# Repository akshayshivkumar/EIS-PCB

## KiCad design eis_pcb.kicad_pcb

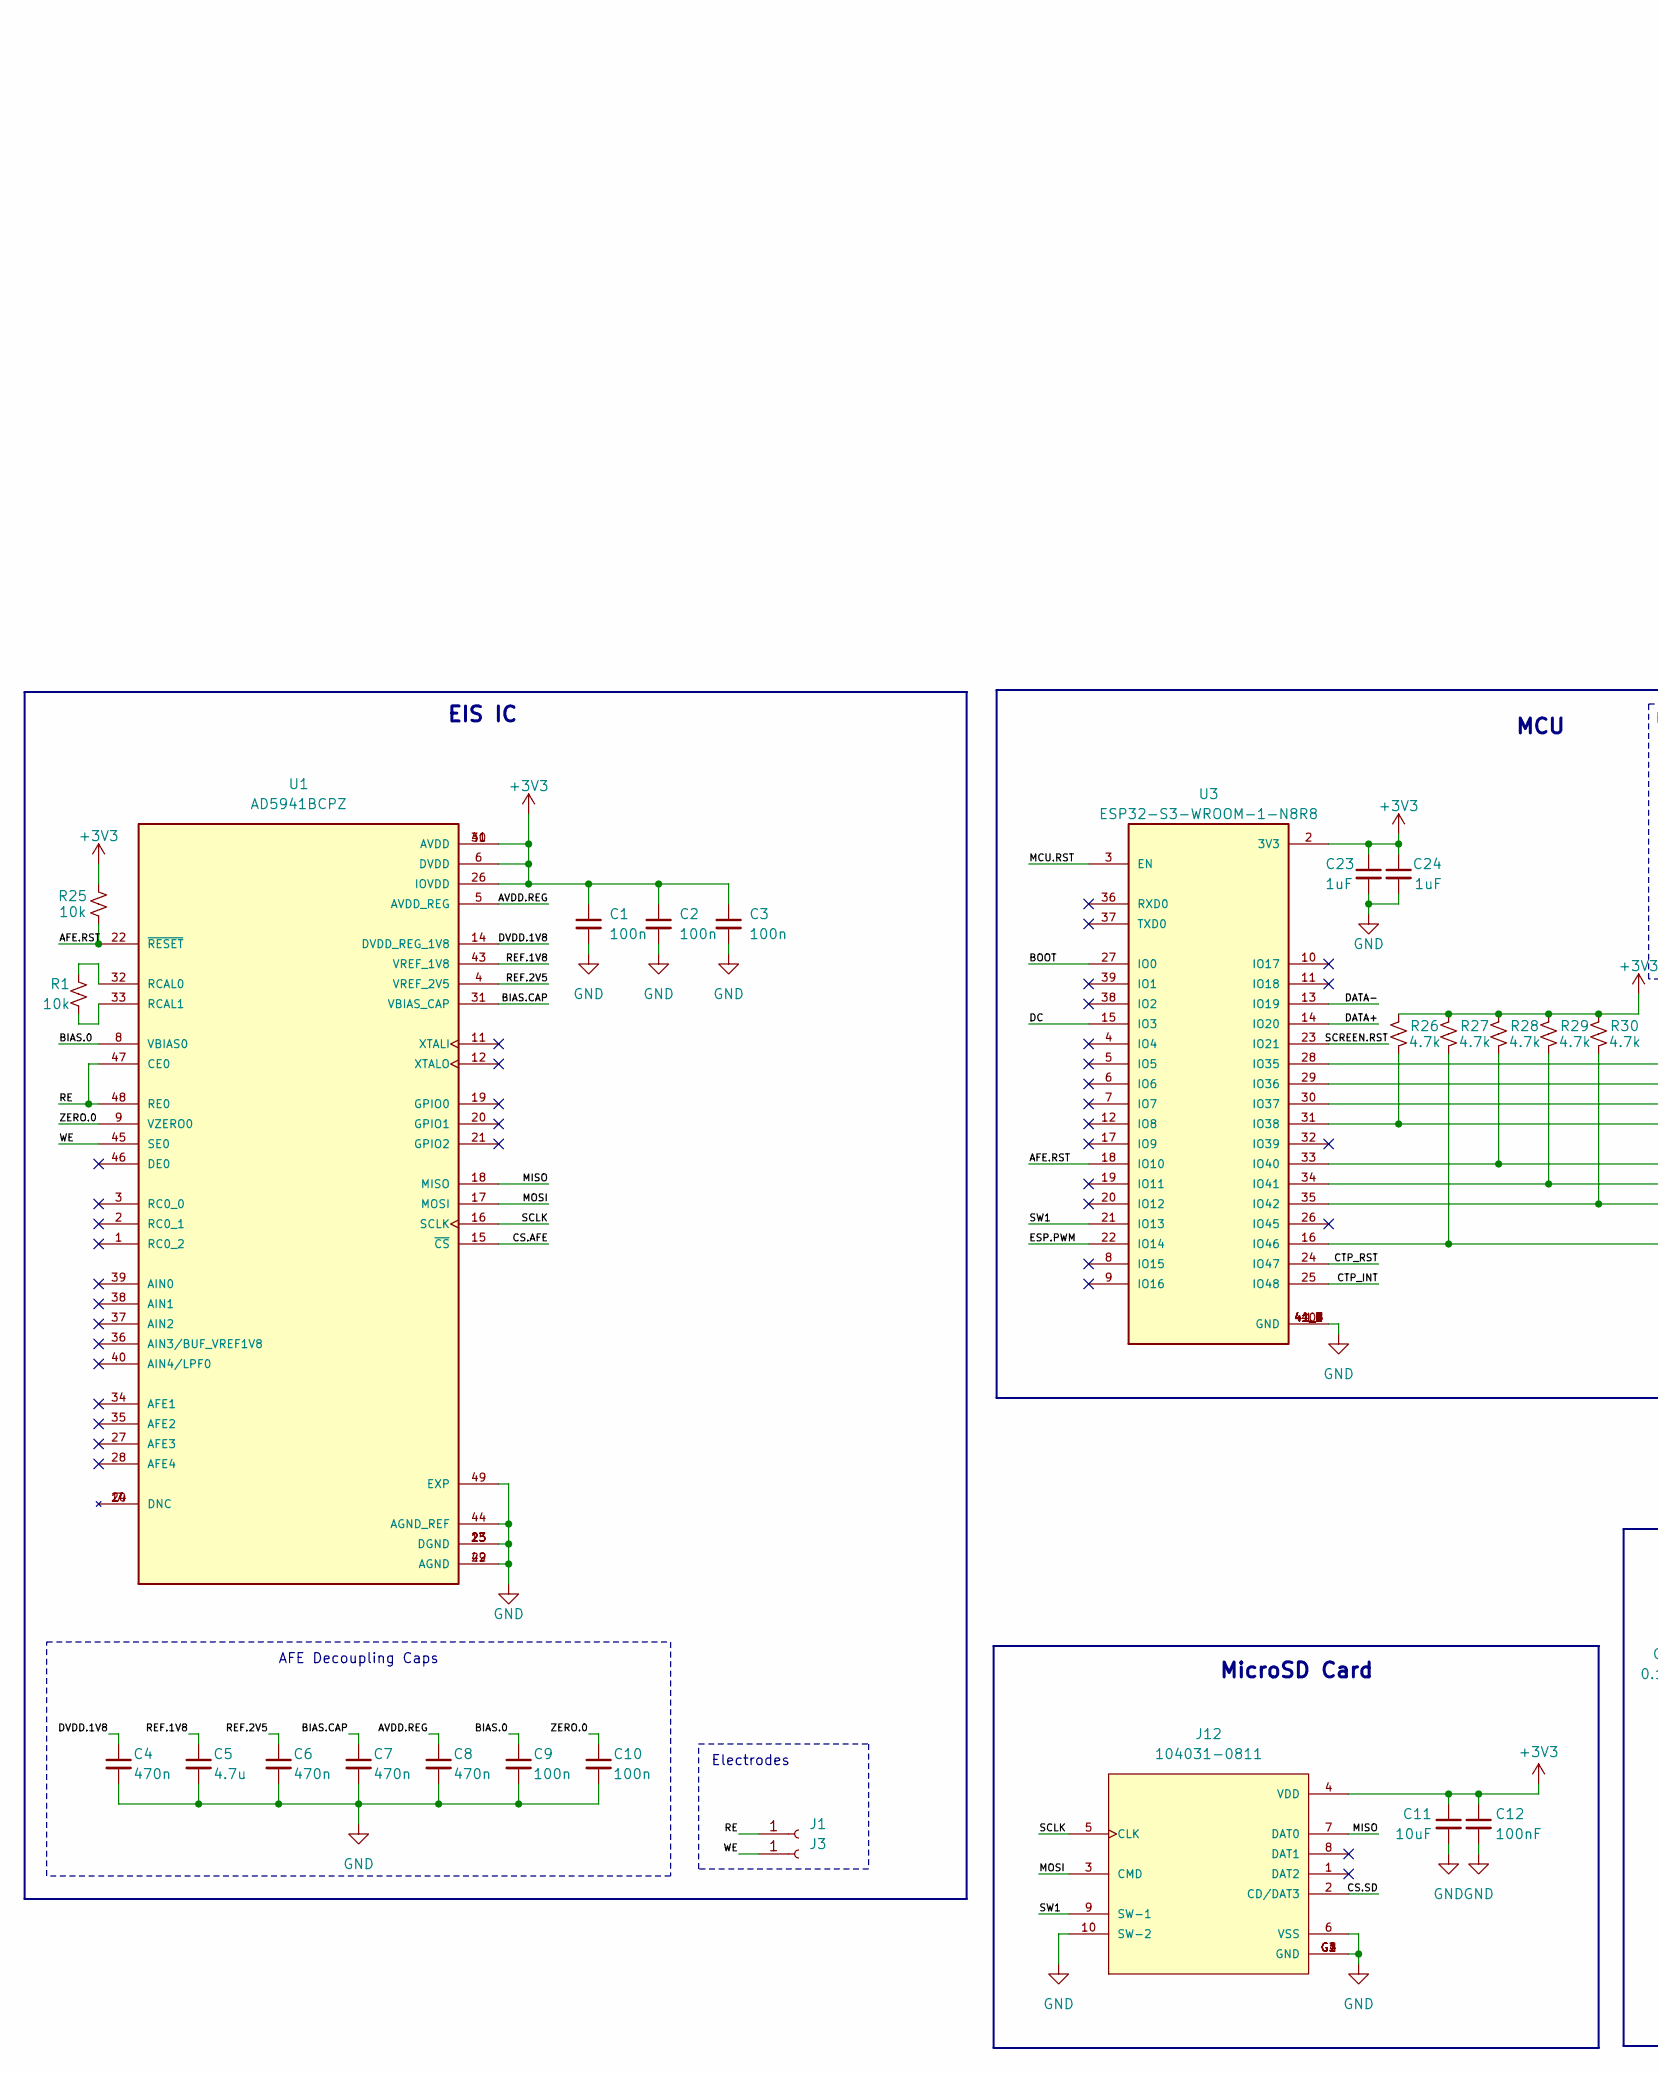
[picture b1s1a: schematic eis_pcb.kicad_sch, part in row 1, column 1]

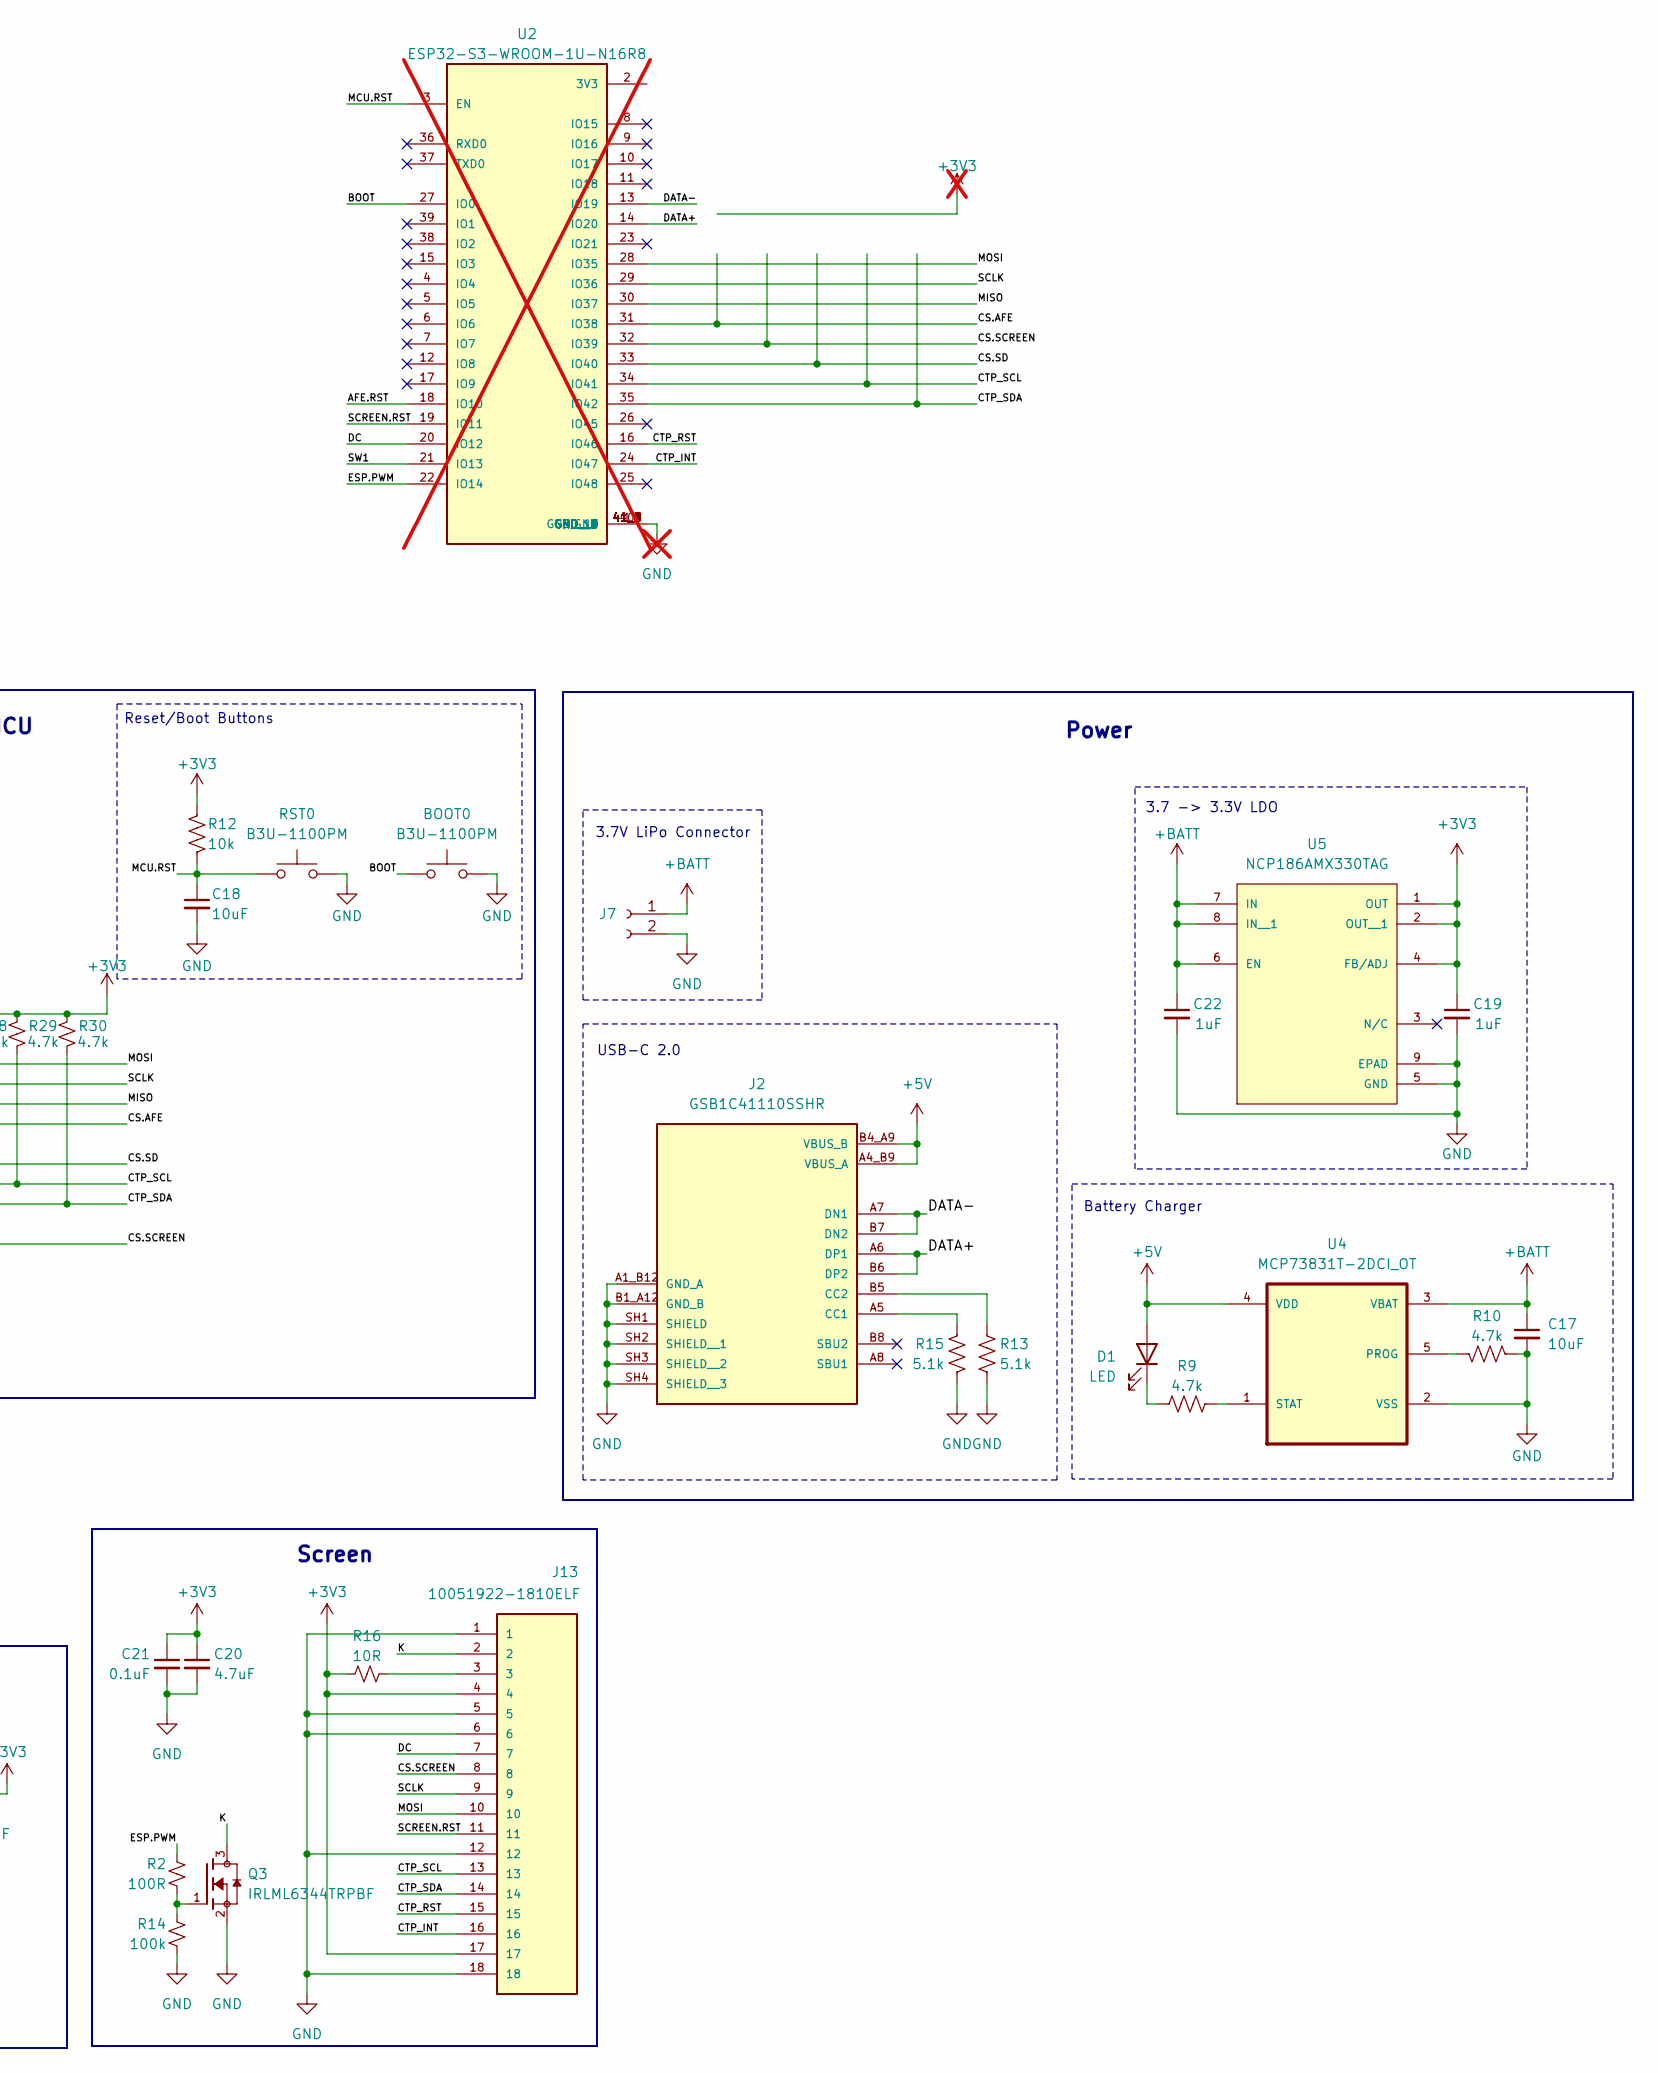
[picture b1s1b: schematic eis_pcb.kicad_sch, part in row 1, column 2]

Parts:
BOOT0: B3U-1100PM; 434121025816
C1, C2, C3, C9, C10: 100n; C_0402_1005Metric
C4, C6, C7, C8: 470n; C_0402_1005Metric
C5: 4.7u; C_0402_1005Metric
C11, C18: 10uF; C_0402_1005Metric
C12: 100nF; C_0402_1005Metric
C17: 10uF; C_0603_1608Metric
C19, C22: 1uF; C_0603_1608Metric
C20: 4.7uF; C_0402_1005Metric
C21: 0.1uF; C_0402_1005Metric
C23, C24: 1uF; C_0402_1005Metric
D1: LED; LED_0603_1608Metric
J1, J3: Conn_01x01_Socket; SolderWirePad_1x01_SMD_1x2mm
J2: GSB1C41110SSHR; AMPHENOL_GSB1C41110SSHR; PARTREV AX1
J7: Conn_01x02_Socket; CONN_S2B-PH-K-S_JST
J12: 104031-0811; MOLEX_104031-0811; PARTREV B2; DigiKey_Part_Number WM6357CT-ND
J13: 10051922-1810ELF; AMPHENOL_10051922-1810ELF; PARTREV J; DigiKey_Part_Number 609-10051922-1810ELFCT-ND
Q3: IRLML6344TRPBF; TRANS_IRLML6344TRPBF; PARTREV December 19, 2014; DigiKey_Part_Number IRLML6344TRPBFCT-ND
R1: 10k; R_0805_2012Metric
R2: 100R; R_0402_1005Metric
R9, R10, R26, R27, R28, R29, R30: 4.7k; R_0402_1005Metric
R12, R25: 10k; R_0402_1005Metric
R13, R15: 5.1k; R_0402_1005Metric
R14: 100k; R_0402_1005Metric
R16: 10R; R_0402_1005Metric
RST0: B3U-1100PM; 434121025816
U1: AD5941BCPZ; QFN50P700X700X80-49N; PARTREV B
U2: ESP32-S3-WROOM-1U-N16R8; XCVR_ESP32-S3-WROOM-1U-N16R8; PARTREV v1.1; not fitted
U3: ESP32-S3-WROOM-1-N8R8; XCVR_ESP32S3WROOM1N8R8; DigiKey_Part_Number 5407-ESP32-S3-WROOM-1-N8R8CT-ND
U4: MCP73831T-2DCI_OT; SOT95P270X145-5N; MPN MCP73831T-2DCI/OT; DigiKey_Part_Number MCP73831T-2DCI/OTCT-ND
U5: NCP186AMX330TAG; PSON40P160X120X45-9N; PARTREV Rev.5

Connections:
+3V3: C1.1, C2.1, C3.1, C11.1, C12.1, C19.1, C20.1, C21.1, C23.1, C24.1, J12.4 (VDD), J13.4, J13.17, R12.1, R16.1, R25.2, R26.2, R27.2, R28.2, R29.2, R30.2, U1.6 (DVDD), U1.26 (IOVDD), U1.30 (AVDD), U1.41 (AVDD), U3.2 (3V3), U5.1 (OUT), U5.2 (OUT__1), U5.4 (FB/ADJ)
+5V: D1.2 (A), J2.A4_B9 (VBUS_A), J2.B4_A9 (VBUS_B), U4.4 (VDD)
+BATT: C17.1, C22.1, J7.1, U4.3 (VBAT), U5.6 (EN), U5.7 (IN), U5.8 (IN__1)
/AFE.RST: R25.1, U1.22 (~RESET), U2.18 (IO10), U3.18 (IO10)
/AVDD.REG: C8.1, U1.5 (AVDD_REG)
/BIAS.0: C9.1, U1.8 (VBIAS0)
/BIAS.CAP: C7.1, U1.31 (VBIAS_CAP)
/BOOT: BOOT0.1, U2.27 (IO0), U3.27 (IO0)
/CS.AFE: R26.1, U1.15 (~CS), U2.31 (IO38), U3.31 (IO38)
/CS.SCREEN: J13.8, R27.1, U2.32 (IO39), U3.16 (IO46)
/CS.SD: J12.2 (CD/DAT3), R28.1, U2.33 (IO40), U3.33 (IO40)
/CTP_INT: J13.16, U2.24 (IO47), U3.25 (IO48)
/CTP_RST: J13.15, U2.16 (IO46), U3.24 (IO47)
/CTP_SCL: J13.13, R29.1, U2.34 (IO41), U3.34 (IO41)
/CTP_SDA: J13.14, R30.1, U2.35 (IO42), U3.35 (IO42)
/DATA+: J2.A6 (DP1), J2.B6 (DP2), U2.14 (IO20), U3.14 (IO20)
/DATA-: J2.A7 (DN1), J2.B7 (DN2), U2.13 (IO19), U3.13 (IO19)
/DC: J13.7, U2.20 (IO12), U3.15 (IO3)
/DVDD.1V8: C4.1, U1.14 (DVDD_REG_1V8)
/ESP.PWM: R2.1, U2.22 (IO14), U3.22 (IO14)
/K: J13.2, Q3.3
/MCU.RST: C18.1, R12.2, RST0.2, U2.3 (EN), U3.3 (EN)
/MISO: J12.7 (DAT0), U1.18 (MISO), U2.30 (IO37), U3.30 (IO37)
/MOSI: J12.3 (CMD), J13.10, U1.17 (MOSI), U2.28 (IO35), U3.28 (IO35)
/RE: J1.1, U1.47 (CE0), U1.48 (RE0)
/REF.1V8: C5.1, U1.43 (VREF_1V8)
/REF.2V5: C6.1, U1.4 (VREF_2V5)
/SCLK: J12.5 (CLK), J13.9, U1.16 (SCLK), U2.29 (IO36), U3.29 (IO36)
/SCREEN.RST: J13.11, U2.19 (IO11), U3.23 (IO21)
/SW1: J12.9 (SW-1), U2.21 (IO13), U3.21 (IO13)
/WE: J3.1, U1.45 (SE0)
/ZERO.0: C10.1, U1.9 (VZERO0)
GND: BOOT0.2, C1.2, C2.2, C3.2, C4.2, C5.2, C6.2, C7.2, C8.2, C9.2, C10.2, C11.2, C12.2, C17.2, C18.2, C19.2, C20.2, C21.2, C22.2, C23.2, C24.2, J2.A1_B12 (GND_A), J2.B1_A12 (GND_B), J2.SH1 (SHIELD), J2.SH2 (SHIELD__1), J2.SH3 (SHIELD__2), J2.SH4 (SHIELD__3), J7.2, J12.6 (VSS), J12.10 (SW-2), J12.G1 (GND), J12.G2 (GND), J12.G3 (GND), J12.G4 (GND), J13.1, J13.5, J13.6, J13.12, J13.18, Q3.2, R10.1, R13.2, R14.2, R15.2, RST0.1, U1.13 (DGND), U1.23 (DGND), U1.25 (DGND), U1.29 (AGND), U1.42 (AGND), U1.44 (AGND_REF), U1.49 (EXP), U2.1 (GND), U2.40 (GND__1), U2.41_1 (GND__2), U2.41_2 (GND__3), U2.41_3 (GND__4), U2.41_4 (GND__5), U2.41_5 (GND__6), U2.41_6 (GND__7), U2.41_7 (GND__8), U2.41_8 (GND__9), U2.41_9 (GND__10), U3.1 (GND), U3.40 (GND), U3.41_1 (GND), U3.41_2 (GND), U3.41_3 (GND), U3.41_4 (GND), U3.41_5 (GND), U3.41_6 (GND), U3.41_7 (GND), U3.41_8 (GND), U3.41_9 (GND), U4.2 (VSS), U5.5 (GND), U5.9 (EPAD)
unnamed: D1.1 (K), R9.1
unnamed: J2.A5 (CC1), R15.1
unnamed: J2.B5 (CC2), R13.1
unnamed: J13.3, R16.2
unnamed: Q3.1, R2.2, R14.1
unnamed: R1.1, U1.32 (RCAL0)
unnamed: R1.2, U1.33 (RCAL1)
unnamed: R10.2, U4.5 (PROG)
unnamed: R9.2, U4.1 (STAT)

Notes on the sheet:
MCU
Screen
AFE Decoupling Caps
3.7 -> 3.3V LDO
USB-C 2.0
EIS IC
Power
Electrodes
Reset/Boot Buttons
MicroSD Card
3.7V LiPo Connector
Battery Charger

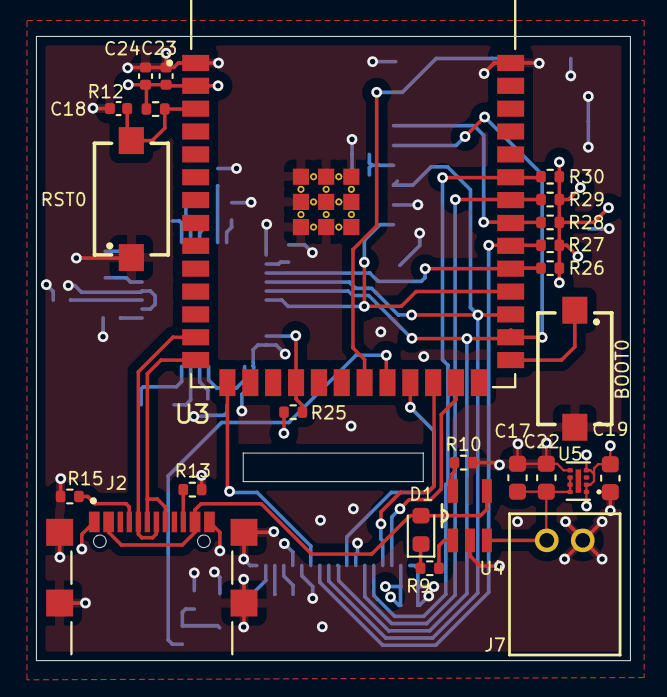
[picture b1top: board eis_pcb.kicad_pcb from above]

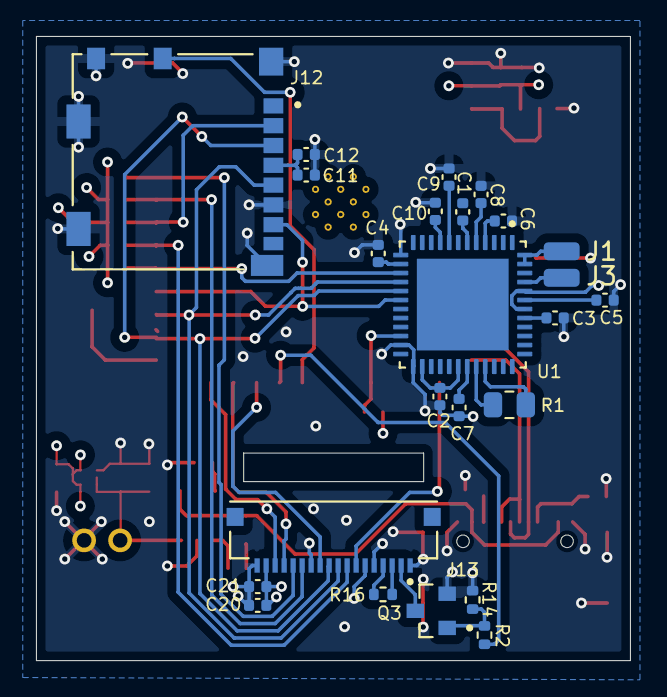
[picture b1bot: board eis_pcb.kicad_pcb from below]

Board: 4 copper layers, 33.0 x 34.7 mm, 49 parts (24 on the bottom side), 42 nets.

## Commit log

2025-11-19 Draft
2025-11-19 Draft 2
2025-11-19 Updated to esp+antenna
2025-11-19 Fixed wiring issues
2025-11-19 Stable version
2025-11-19 Improved wiring
